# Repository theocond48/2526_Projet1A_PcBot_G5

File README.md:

# 2526_Projet1A_PcBot_G5

**Objectif :** Concevoir un robot communicant (Swarm) pour la cartographie d'environnement.
**Volume horaire :** 40 heures (10 séances x 4h).

- Travail en groupe réalisé par: Youssef Chemrakhi, Théodore Condette, Rayan Taoussi, Samy, Maroua Qidi.

# I - Phase 1 : Conception et Saisie de Schéma
- **Séance 1 : Initialisation & Spécifications**

- **Définition du Besoin**
  - Liste des fonctionnalités
  - Schéma architectural
- **Planification et Matériel**
  - Planning prévisionnel
  - Choix des composants

# 1 - Liste des fonctionnalités
Le robot doit être capable de:
- **Navigation et Évitement d'obstacles :** Détection d'objets en temps réel via les capteurs **VL53L0X (TOF)** pour ajuster la trajectoire.
- **Localisation Relative:** Suivi du déplacement et de l'orientation grâce à la centrale inertielle **LSM6DSOX** (Accéléromètre/Gyroscope).
- **Cartographie Collaborative :** Envoi des points de données de l'environnement vers les autres robots ou une station de base via le module **nRF24**.
- **Gestion de Swarm :** Capacité à recevoir des instructions ou à partager sa position pour éviter que deux robots ne couvrent la même zone.
- **Pilotage de Puissance :** Contrôle précis de la vitesse et de la direction des micro-moteurs **DFR1224** via le driver **DRV8411A**.
- **Autonomie Énergétique :** Recharge sécurisée de la batterie Li-ion et monitoring de la tension via le contrôleur **BQ25896**.

## 1.2 -Détails des composants 

## BMS bq25896

- **C'est quoi ?** Le gestionnaire d'énergie intelligent.
    
- **Sa mission :**
    
    1. Il prend le 5V de l'USB pour charger la batterie LiPo en toute sécurité.
        
    2. Il protège la batterie (surcharge/décharge profonde).
        
    3. Il fournit l'énergie principale (SYS) au reste du robot.
        
- **Pourquoi c'est vital ?** Sans lui, ta batterie LiPo pourrait prendre feu ou mourir prématurément.

### Pin configuration BMS :

**Netlist:**

## Motor's Driver DRV8411A 

- **C'est quoi ?** L'amplificateur de puissance.
    
- **Sa mission :** Le STM32 est trop faible pour faire tourner les moteurs directement. Le DRV8411A prend les petits ordres logiques (3.3V) et ouvre les vannes du "gros courant" venant de la batterie pour faire tourner les roues.
    
- **Pourquoi c'est vital ?** Il protège le STM32 des retours de courant inductif des moteurs.
### Pin configuration Driver

## imu adafruit (centrale inertielle)

 LSM6DSOX (IMU - Accéléromètre/Gyroscope)

- **C'est quoi ?** Le capteur d'équilibre et de mouvement.
    
- **Sa mission :** Il sent si le robot accélère, tourne, ou s'il cogne un mur (choc). Il permet de faire avancer le robot bien droit (en corrigeant la trajectoire si une roue tourne plus vite que l'autre).
    
### Pin configuration imu

## Tof vl53lx
VL53L0X (ToF - Time of Flight)

- **C'est quoi ?** Le télémètre laser.
    
- **Sa mission :** Il envoie un rayon de lumière invisible (infrarouge) et mesure le temps qu'il met à revenir. Cela lui donne la distance précise de l'obstacle devant lui (en millimètres).

### Pin configuration tof

VL53L0X (ToF - Time of Flight)

- **C'est quoi ?** Le télémètre laser.
    
- **Sa mission :** Il envoie un rayon de lumière invisible (infrarouge) et mesure le temps qu'il met à revenir. Cela lui donne la distance précise de l'obstacle devant lui (en millimètres).

## motor DFR1224
(Moteurs N20 3V)

- **C'est quoi ?** Les actionneurs.
    
- **Sa mission :** Convertir l'électricité en mouvement mécanique. Ils ont une boîte de vitesses (engrenages) intégrée pour avoir du couple (force) plutôt que de la vitesse pure.
    
- **Rappel critique :** Ce sont des moteurs **3V**. Ils doivent être alimentés avec précaution via le PWM du driver.

## module de communication nRF24l01

### Pin configuration nrf

**Netlist**

# 2 - Schéma architectural

Le schéma ci-dessous illustre l'organisation du système. Le microcontrôleur (MCU) agit comme le cerveau central, coordonnant les capteurs (entrées), les actionneurs (sorties) et la communication.

```mermaid
graph TD
    %% Alimentation
    subgraph Power_System [Gestion Énergie]
        BAT[Batterie Li-ion] --- BMS[BMS: BQ25896]
        BMS -- I2C --> MCU[STM32L476]
    end

    %% Capteurs
    subgraph Perception [Capteurs / Entrées]
        TOF[Télémètres: VL53L0X] -- I2C --> MCU
        IMU[Centrale Inertielle: LSM6DSOX] -- I2C --> MCU
    end

    %% Communication
    subgraph Comms [Lien Essaim]
        nRF[Radio: nRF24L01] <-->|SPI| MCU
    end

    %% Actionneurs
    subgraph Motion [Actionneurs / Sorties]
        MCU -- PWM --> DRV[Driver: DRV8411]
        DRV --> M1[Moteur Gauche: DFR1224]
        DRV --> M2[Moteur Droit: DFR1224]
    end

    %% Styles
    style MCU fill:#f9f,stroke:#333,stroke-width:2px
    style BMS fill:#dfd
    style nRF fill:#ddf
```

Afin d'assurer les connexions données, on se reposera sur la Datasheet qui nous donne l'ensembles des ports de la STM32L476 qui sont configurés en I2C et SPI:

# 3 - Planning Prévisionnel - Projet PCBot

## Phase 1 : Conception et Saisie de Schéma
- **Séance 1 : Initialisation & Spécifications**
  - Formation du groupe.
  - Création du dépôt Git et ajout du professeur (laurent.fiack@ensea.fr).
  - Étude des composants : Capteurs TOF, Accéléromètre, nRF24, Batterie/Chargeur.
- **Séance 2 : Saisie de schéma**
  - Début de la saisie sur KiCad des blocs d'alimentation et du microcontrôleur.
- **Séance 3 : Revue de schéma & Finalisation**
  - Revue critique des connexions.
  - Finalisation du schéma complet avant les vacances de février.

## Phase 2 : Routage et Fabrication
- **Séance 4 : Placement et Routage**
  - Placement des composants sur le PCB.
  - Routage des pistes.
- **Séance 5 : Revue de routage & Commande**
  - **Critique :** Validation finale du routage.
  - Génération et envoi des fichiers de fabrication (Gerber).

## Phase 3 : Firmware et Intégration
- **Séance 6 : Tests préliminaires & Firmware**
  - Tests sur cartes de développement.
  - Développement des drivers pour les capteurs TOF et le module nRF24.
- **Séance 7 : Développement Firmware**
  - Implémentation des algorithmes de cartographie et de communication Swarm.
- **Séance 8 : Firmware & Soudure**
  - Réception possible des PCB.
  - Assemblage (soudure) et tests de continuité.
- **Séance 9 : Intégration Finale & Débogage**
  - Tests en conditions réelles du robot.
  - Correction des derniers bugs du firmware.

## Phase 4 : Clôture
- **Séance 10 : Finitions & Démo**
  - 2h : Préparation finale et finitions.
  - 2h : Présentation et démonstration du projet.

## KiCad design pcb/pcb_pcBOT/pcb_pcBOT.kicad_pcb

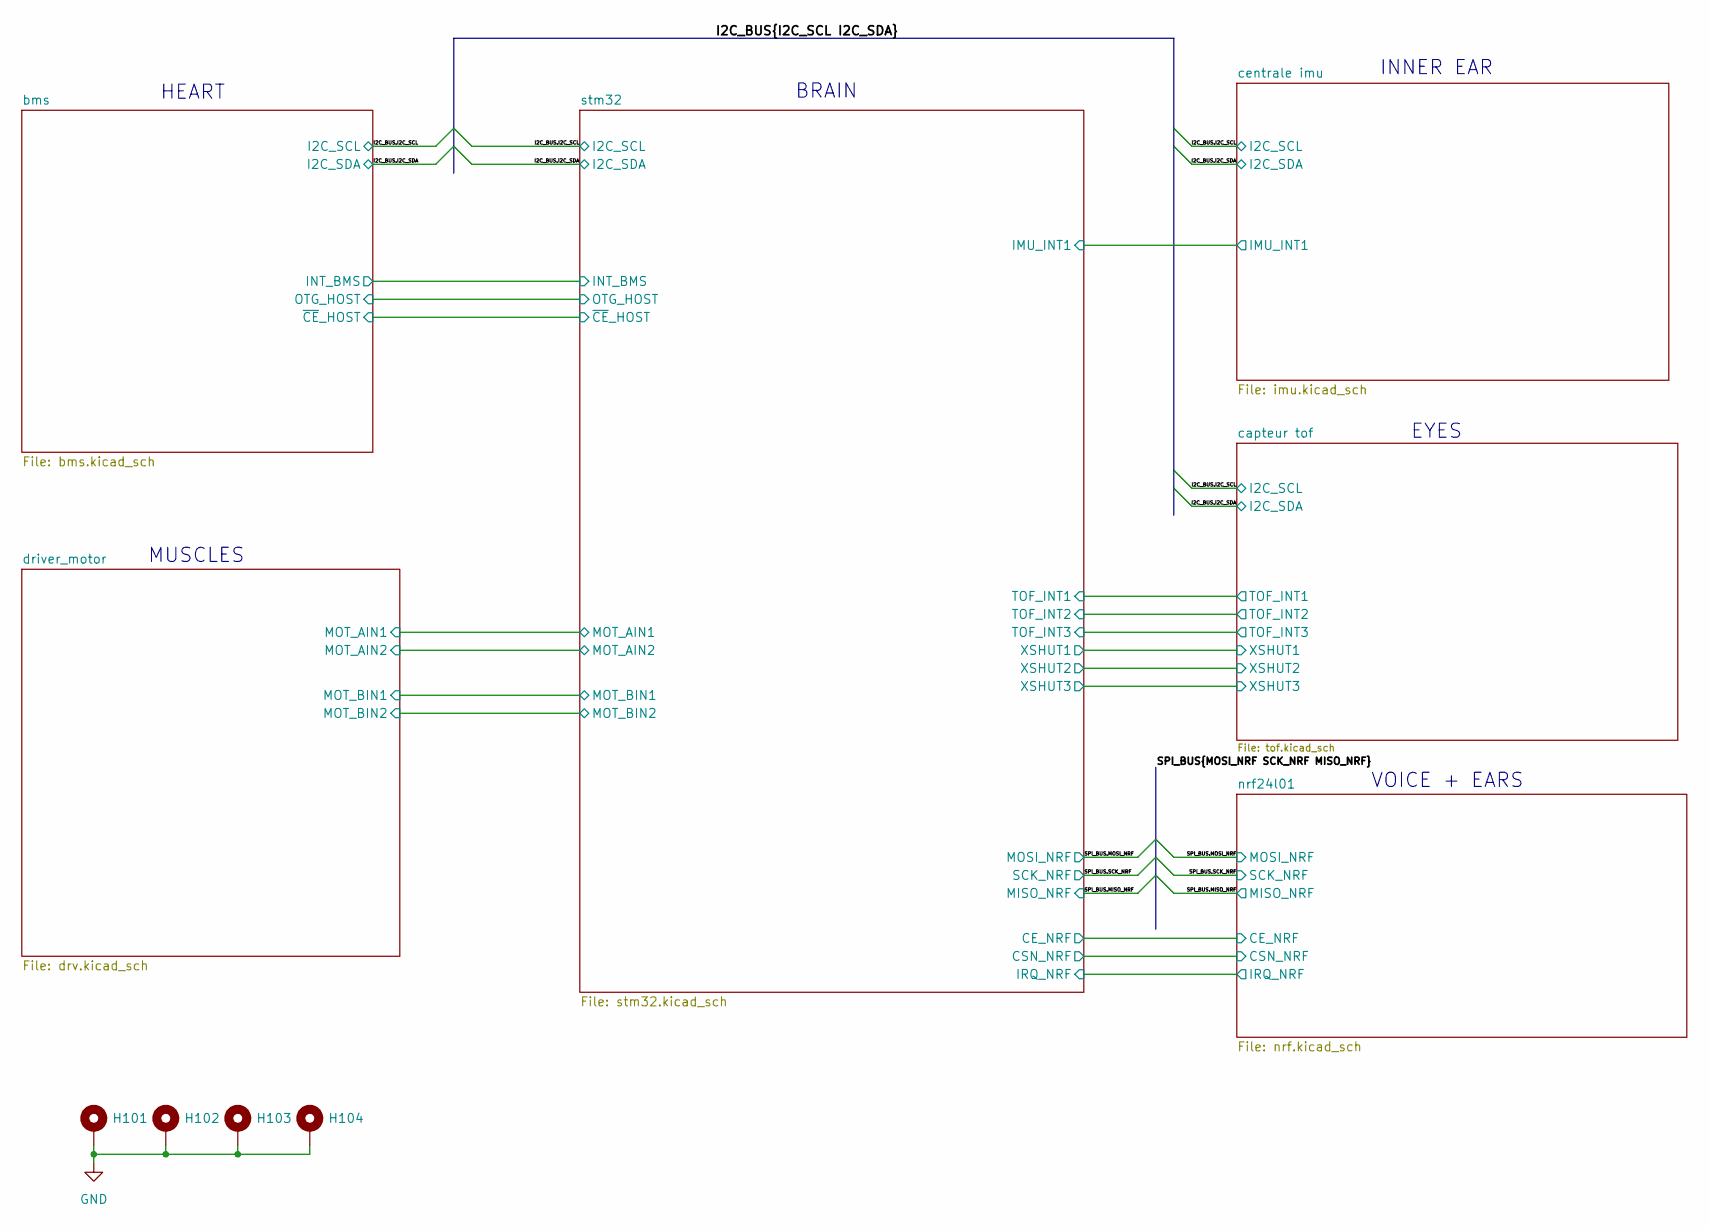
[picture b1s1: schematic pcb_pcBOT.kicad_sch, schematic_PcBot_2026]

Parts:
H101, H102, H103, H104: MountingHole_Pad; MountingHole_3.2mm_M3_Pad_Via

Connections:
GND: H101.1, H102.1, H103.1, H104.1; also elsewhere on the board

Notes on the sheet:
BRAIN
EYES
HEART
VOICE + EARS
INNER EAR
MUSCLES

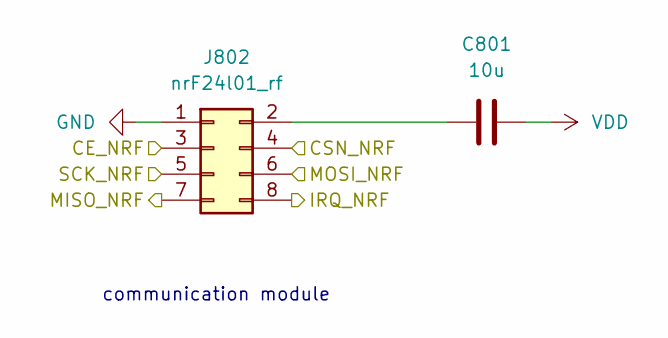
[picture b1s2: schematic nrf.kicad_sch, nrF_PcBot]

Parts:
C801: 10u; C_0603_1608Metric
J802: nrF24l01_rf; PinHeader_2x04_P2.54mm_Vertical

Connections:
/SPI_BUS.MISO_NRF: J802.7; also elsewhere on the board
/SPI_BUS.MOSI_NRF: J802.6; also elsewhere on the board
/SPI_BUS.SCK_NRF: J802.5; also elsewhere on the board
/nrf24l01/CE_NRF: J802.3; also elsewhere on the board
/nrf24l01/CSN_NRF: J802.4; also elsewhere on the board
/nrf24l01/IRQ_NRF: J802.8; also elsewhere on the board
GND: J802.1; also elsewhere on the board
unnamed: C801.1, J802.2
VDD: C801.2; also elsewhere on the board

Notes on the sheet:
communication module

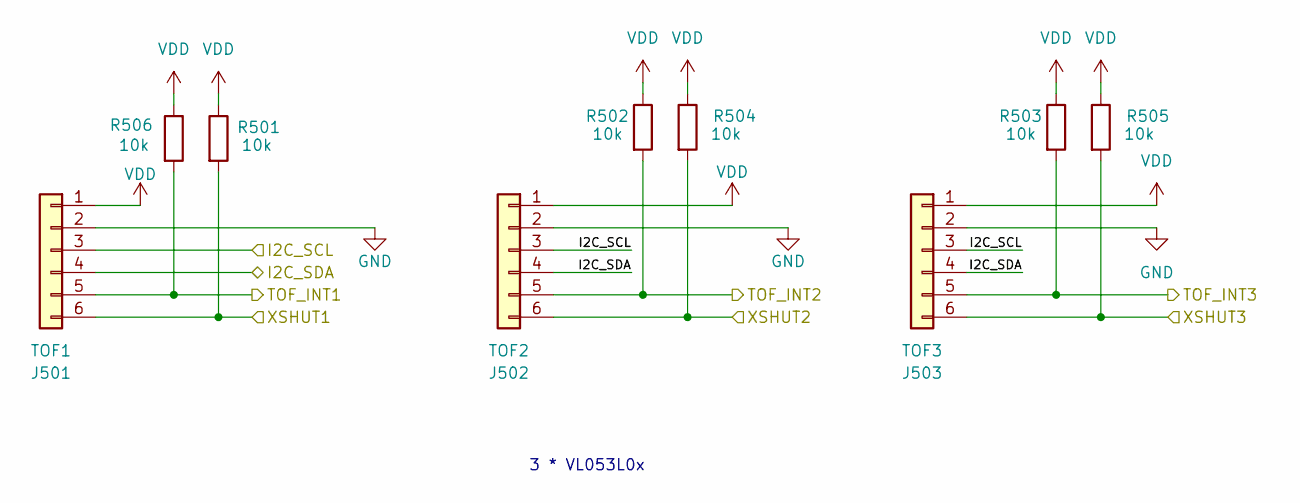
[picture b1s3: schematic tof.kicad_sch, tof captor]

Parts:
J501: TOF1; PinSocket_1x06_P2.54mm_Vertical
J502: TOF2; PinSocket_1x06_P2.54mm_Vertical
J503: TOF3; PinSocket_1x06_P2.54mm_Vertical
R501, R502, R503, R504, R505, R506: 10k; R_0402_1005Metric

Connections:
/I2C_BUS.I2C_SCL: J501.3, J502.3, J503.3; also elsewhere on the board
/I2C_BUS.I2C_SDA: J501.4, J502.4, J503.4; also elsewhere on the board
/capteur tof/TOF_INT1: J501.5, R506.2; also elsewhere on the board
/capteur tof/TOF_INT2: J502.5, R502.2; also elsewhere on the board
/capteur tof/TOF_INT3: J503.5, R503.2; also elsewhere on the board
/capteur tof/XSHUT1: J501.6, R501.2; also elsewhere on the board
/capteur tof/XSHUT2: J502.6, R504.2; also elsewhere on the board
/capteur tof/XSHUT3: J503.6, R505.2; also elsewhere on the board
GND: J501.2, J502.2, J503.2; also elsewhere on the board
VDD: J501.1, J502.1, J503.1, R501.1, R502.1, R503.1, R504.1, R505.1, R506.1; also elsewhere on the board

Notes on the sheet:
3 * VL053L0x

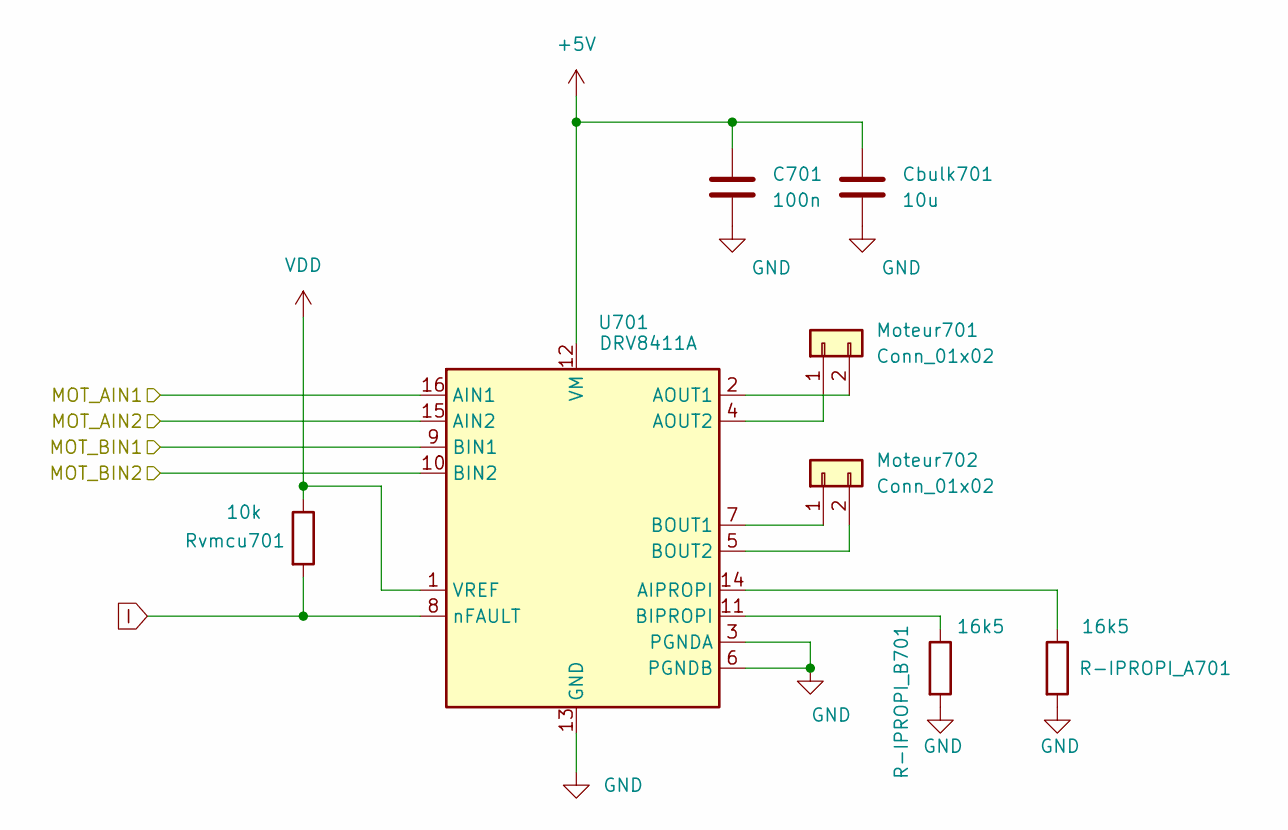
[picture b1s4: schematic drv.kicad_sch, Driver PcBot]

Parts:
C701: 100n; C_0402_1005Metric
Cbulk701: 10u; C_0603_1608Metric
Moteur701, Moteur702: Conn_01x02; JST_PH_B2B-PH-K_1x02_P2.00mm_Vertical
R-IPROPI_A701: 16k5; R_0402_1005Metric
R-IPROPI_B701: 16k5; R_0402_1005Metric
Rvmcu701: 10k; R_0402_1005Metric
U701: DRV8411A; HTSSOP-16-1EP_4.4x5mm_P0.65mm_EP3.4x5mm_Mask2.46x2.31mm_The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

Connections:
+5V: C701.2, Cbulk701.1, U701.12 (VM); also elsewhere on the board
/driver_motor/MOT_AIN1: U701.16 (AIN1); also elsewhere on the board
/driver_motor/MOT_AIN2: U701.15 (AIN2); also elsewhere on the board
/driver_motor/MOT_BIN1: U701.9 (BIN1); also elsewhere on the board
/driver_motor/MOT_BIN2: U701.10 (BIN2); also elsewhere on the board
GND: C701.1, Cbulk701.2, R-IPROPI_A701.2, R-IPROPI_B701.2, U701.3 (PGNDA), U701.6 (PGNDB), U701.13 (GND), U701.17 (PPAD); also elsewhere on the board
I: Rvmcu701.2, U701.8 (nFAULT)
unnamed: Moteur701.1, U701.4 (AOUT2)
unnamed: Moteur701.2, U701.2 (AOUT1)
unnamed: Moteur702.1, U701.7 (BOUT1)
unnamed: Moteur702.2, U701.5 (BOUT2)
unnamed: R-IPROPI_A701.1, U701.14 (AIPROPI)
unnamed 52: R-IPROPI_B701.1, U701.11 (BIPROPI); also elsewhere on the board
VDD: Rvmcu701.1, U701.1 (VREF); also elsewhere on the board

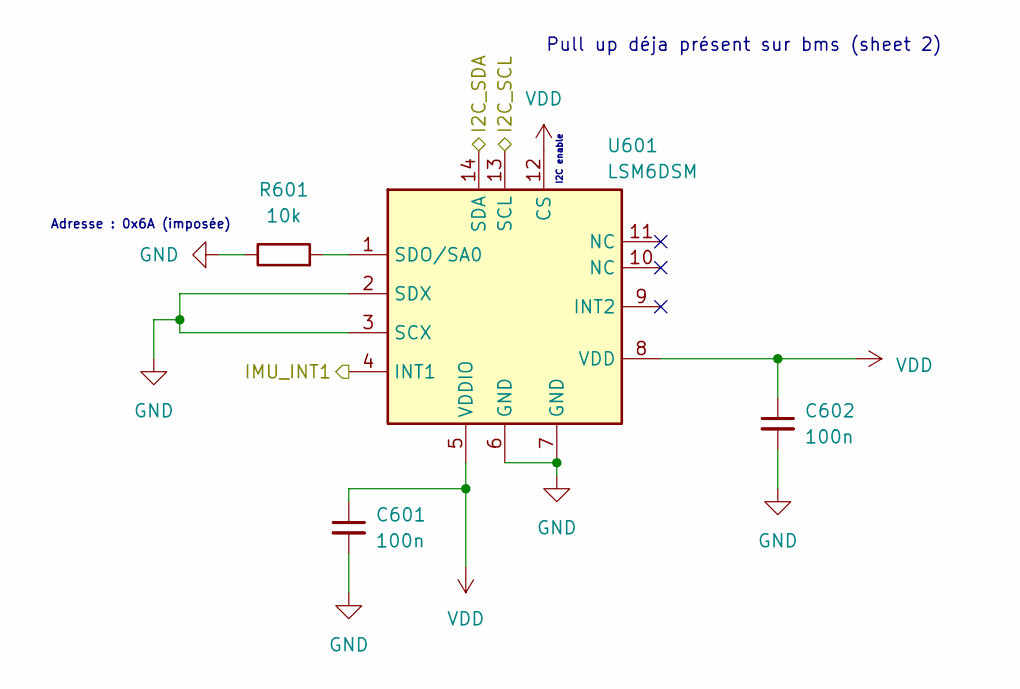
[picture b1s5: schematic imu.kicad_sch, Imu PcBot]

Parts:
C601, C602: 100n; C_0402_1005Metric
R601: 10k; R_0402_1005Metric
U601: LSM6DSM; LGA-14_3x2.5mm_P0.5mm_LayoutBorder3x4y

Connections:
/I2C_BUS.I2C_SCL: U601.13 (SCL); also elsewhere on the board
/I2C_BUS.I2C_SDA: U601.14 (SDA); also elsewhere on the board
/centrale imu/IMU_INT1: U601.4 (INT1); also elsewhere on the board
GND: C601.2, C602.2, R601.1, U601.2 (SDX), U601.3 (SCX), U601.6 (GND), U601.7 (GND); also elsewhere on the board
unnamed: R601.2, U601.1 (SDO/SA0)
VDD: C601.1, C602.1, U601.5 (VDDIO), U601.8 (VDD), U601.12 (CS); also elsewhere on the board

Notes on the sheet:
I2C enable
Pull up déja présent sur bms (sheet 2)
Adresse : 0x6A (imposée)

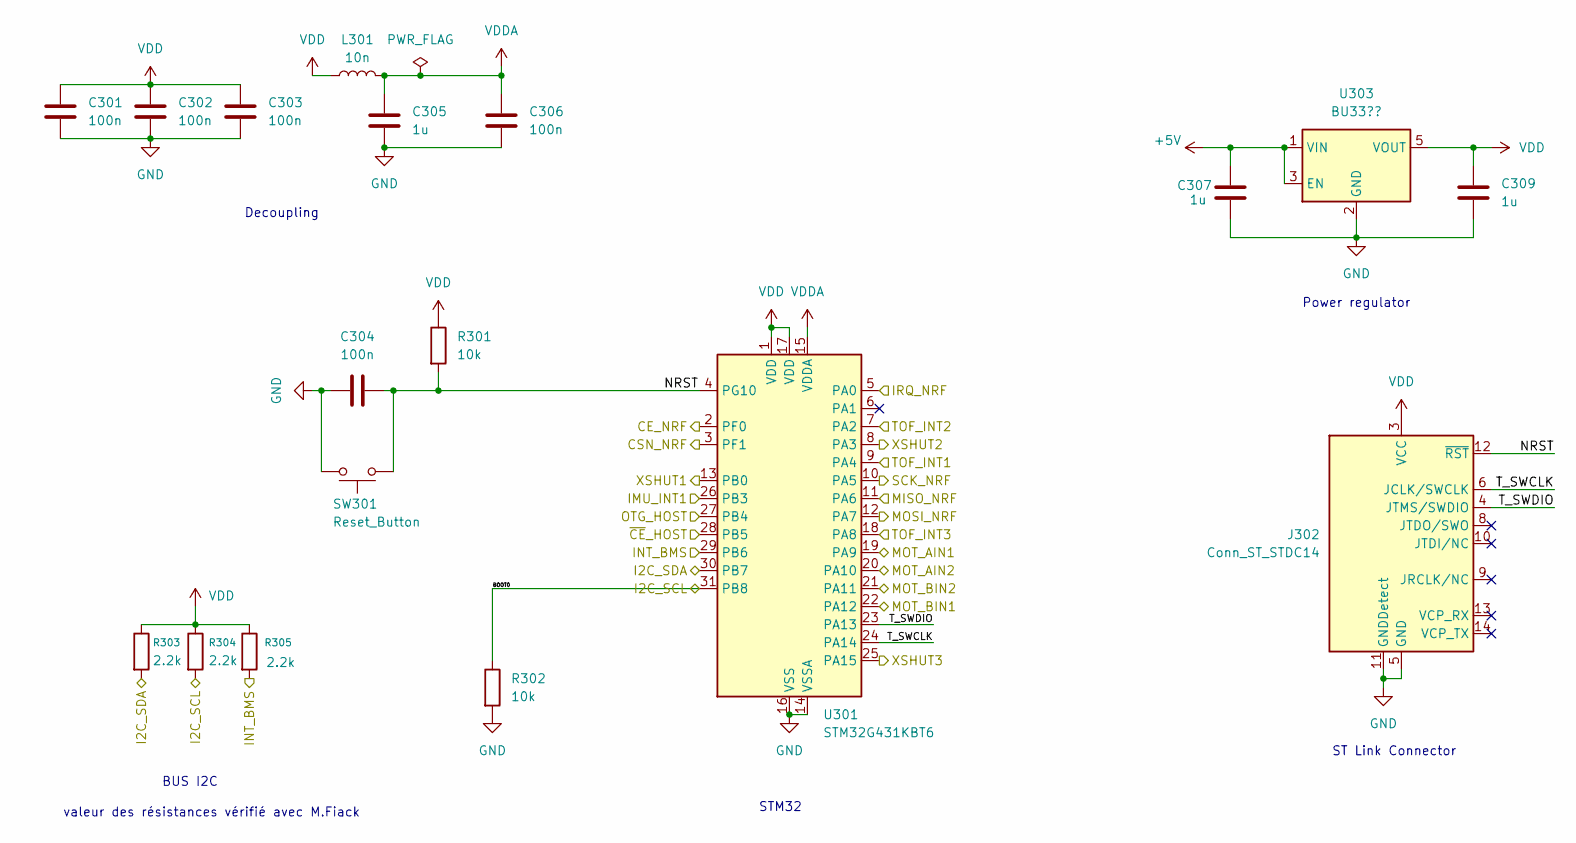
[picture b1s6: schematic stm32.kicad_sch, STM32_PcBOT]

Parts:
C301, C302, C303, C304, C306: 100n; C_0402_1005Metric
C305, C307, C309: 1u; C_0402_1005Metric
J302: Conn_ST_STDC14; PinHeader_2x07_P1.27mm_Vertical_SMD
L301: 10n; C_0603_1608Metric
R301, R302: 10k; R_0402_1005Metric
R303, R304, R305: 2.2k; R_0402_1005Metric
SW301: Reset_Button; SW_PUSH_6mm
U301: STM32G431KBT6; LQFP-32_7x7mm_P0.8mm
U303: BU33??; TSOT-23-5

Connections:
+5V: C307.1, U303.1 (VIN), U303.3 (EN); also elsewhere on the board
/I2C_BUS.I2C_SCL: R302.1, R304.2, U301.31 (PB8); also elsewhere on the board
/I2C_BUS.I2C_SDA: R303.2, U301.30 (PB7); also elsewhere on the board
/SPI_BUS.MISO_NRF: U301.11 (PA6); also elsewhere on the board
/SPI_BUS.MOSI_NRF: U301.12 (PA7); also elsewhere on the board
/SPI_BUS.SCK_NRF: U301.10 (PA5); also elsewhere on the board
/bms/INT_BMS: R305.2, U301.29 (PB6); also elsewhere on the board
/bms/OTG_HOST: U301.27 (PB4); also elsewhere on the board
/bms/~CE_HOST: U301.28 (PB5); also elsewhere on the board
/capteur tof/TOF_INT1: U301.9 (PA4); also elsewhere on the board
/capteur tof/TOF_INT2: U301.7 (PA2); also elsewhere on the board
/capteur tof/TOF_INT3: U301.18 (PA8); also elsewhere on the board
/capteur tof/XSHUT1: U301.13 (PB0); also elsewhere on the board
/capteur tof/XSHUT2: U301.8 (PA3); also elsewhere on the board
/capteur tof/XSHUT3: U301.25 (PA15); also elsewhere on the board
/centrale imu/IMU_INT1: U301.26 (PB3); also elsewhere on the board
/driver_motor/MOT_AIN1: U301.19 (PA9); also elsewhere on the board
/driver_motor/MOT_AIN2: U301.20 (PA10); also elsewhere on the board
/driver_motor/MOT_BIN1: U301.22 (PA12); also elsewhere on the board
/driver_motor/MOT_BIN2: U301.21 (PA11); also elsewhere on the board
/nrf24l01/CE_NRF: U301.2 (PF0); also elsewhere on the board
/nrf24l01/CSN_NRF: U301.3 (PF1); also elsewhere on the board
/nrf24l01/IRQ_NRF: U301.5 (PA0); also elsewhere on the board
/stm32/NRST: C304.1, J302.12 (~RST), R301.2, SW301.1, U301.4 (PG10)
/stm32/T_SWCLK: J302.6 (JCLK/SWCLK), U301.24 (PA14)
/stm32/T_SWDIO: J302.4 (JTMS/SWDIO), U301.23 (PA13)
GND: C301.2, C302.2, C303.2, C304.2, C305.2, C306.2, C307.2, C309.2, J302.5 (GND), J302.7 (GND), J302.11 (GNDDetect), R302.2, SW301.2, U301.14 (VSSA), U301.16 (VSS), U301.32 (VSS), U303.2 (GND); also elsewhere on the board
VDD: C301.1, C302.1, C303.1, C309.1, J302.3 (VCC), L301.1, R301.1, R303.1, R304.1, R305.1, U301.1 (VDD), U301.17 (VDD), U303.5 (VOUT); also elsewhere on the board
VDDA: C305.1, C306.1, L301.2, U301.15 (VDDA)

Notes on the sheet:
ST Link Connector
BUS I2C
Decoupling
valeur des résistances vérifié avec M.Fiack
Power regulator
STM32

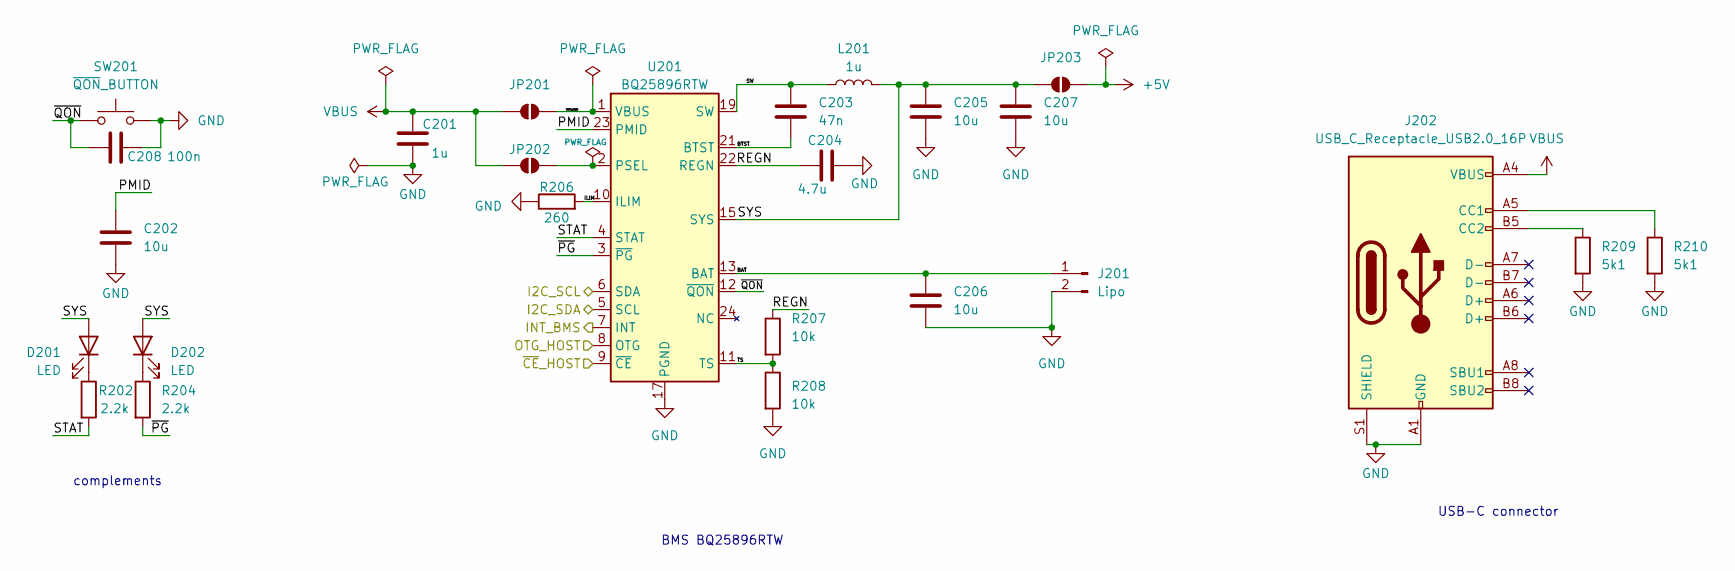
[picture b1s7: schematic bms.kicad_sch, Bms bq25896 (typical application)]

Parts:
C201: 1u; C_0402_1005Metric
C202, C205, C206, C207: 10u; C_0603_1608Metric
C203: 47n; C_0402_1005Metric
C204: 4.7u; C_0603_1608Metric
C208: 100n; C_0402_1005Metric
D201, D202: LED; C_0402_1005Metric
J201: Lipo; JST_PH_B2B-PH-K_1x02_P2.00mm_Vertical
J202: USB_C_Receptacle_USB2.0_16P; USB_C_Receptacle_GCT_USB4105-xx-A_16P_TopMnt_Horizontal
JP201, JP202, JP203: SolderJumper_2_Open; SolderJumper-2_P1.3mm_Open_TrianglePad1.0x1.5mm
L201: 1u; L_1008_2520Metric
R202, R204: 2.2k; R_0402_1005Metric
R206: 260; R_0402_1005Metric
R207, R208: 10k; R_0402_1005Metric
R209, R210: 5k1; R_0402_1005Metric
SW201: ~{QON}_BUTTON; SW_PUSH_6mm
U201: BQ25896RTW; Texas_RTW_WQFN-24-1EP_4x4mm_P0.5mm_EP2.7x2.7mm_ThermalVias

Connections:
+5V: JP203.2 (B); also elsewhere on the board
/I2C_BUS.I2C_SCL: U201.6 (SDA); also elsewhere on the board
/I2C_BUS.I2C_SDA: U201.5 (SCL); also elsewhere on the board
/bms/BAT: C206.1, J201.1, U201.13 (BAT), U201.14 (BAT)
/bms/BTST: C203.2, U201.21 (BTST)
/bms/ILIM: R206.2, U201.10 (ILIM)
/bms/INT_BMS: U201.7 (INT); also elsewhere on the board
/bms/OTG_HOST: U201.8 (OTG); also elsewhere on the board
/bms/PMID: C202.1, U201.23 (PMID)
/bms/REGN: C204.2, R207.1, U201.22 (REGN)
/bms/STAT: R202.2, U201.4 (STAT)
/bms/SW: C203.1, L201.1, U201.19 (SW), U201.20 (SW)
/bms/SYS: C205.1, C207.1, D201.2 (A), D202.2 (A), JP203.1 (A), L201.2, U201.15 (SYS), U201.16 (SYS)
/bms/TS: R207.2, R208.1, U201.11 (TS)
/bms/VBUS_BQ25: JP201.2 (B), U201.1 (VBUS)
/bms/~CE_HOST: U201.9 (~CE); also elsewhere on the board
/bms/~PG: R204.2, U201.3 (~PG)
/bms/~QON: C208.1, SW201.1, U201.12 (~QON)
GND: C201.2, C202.2, C204.1, C205.2, C206.2, C207.2, C208.2, J201.2, J202.A1 (GND), J202.A12 (GND), J202.B1 (GND), J202.B12 (GND), J202.S1 (SHIELD), R206.1, R208.2, R209.2, R210.2, SW201.2, U201.17 (PGND), U201.18 (PGND), U201.25 (PGND); also elsewhere on the board
unnamed: D201.1 (K), R202.1
unnamed: D202.1 (K), R204.1
unnamed: J202.A5 (CC1), R210.1
unnamed: J202.B5 (CC2), R209.1
unnamed: JP202.2 (B), U201.2 (PSEL)
VBUS: C201.1, J202.A4 (VBUS), J202.A9 (VBUS), J202.B4 (VBUS), J202.B9 (VBUS), JP201.1 (A), JP202.1 (A)

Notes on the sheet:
USB-C connector
BMS BQ25896RTW
complements

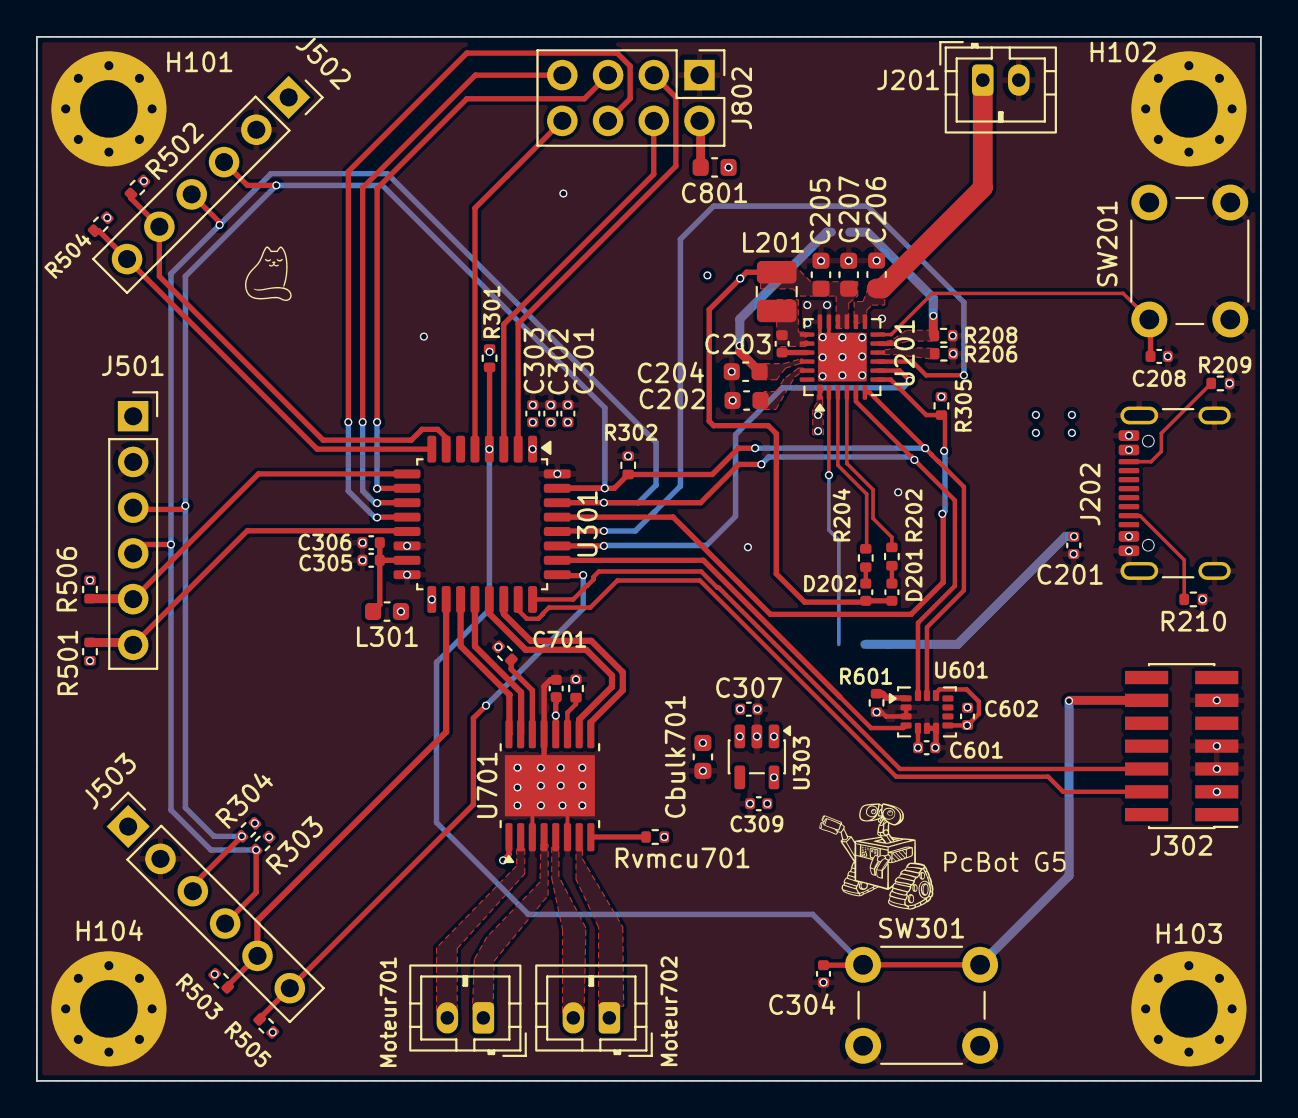
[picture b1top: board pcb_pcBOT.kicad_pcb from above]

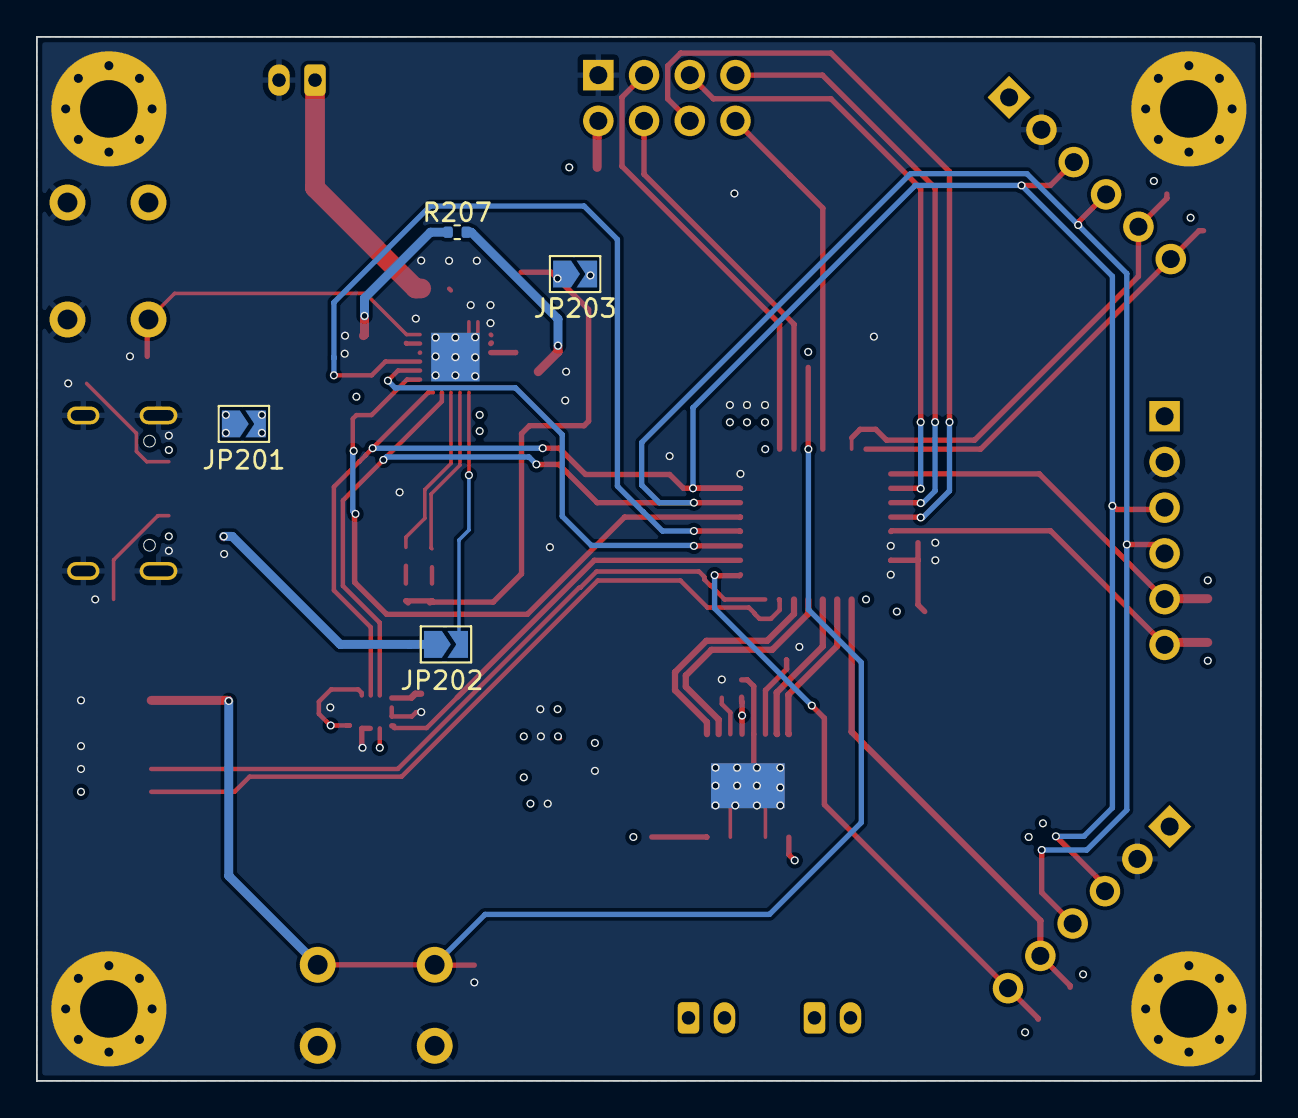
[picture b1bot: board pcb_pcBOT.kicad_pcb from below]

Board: 4 copper layers, 68.0 x 58.0 mm, 70 parts (4 on the bottom side), 56 nets.

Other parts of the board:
R-B701: 16k5; R_0402_1005Metric

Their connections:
GND: R-B701.2; also elsewhere on the board
unnamed 52: R-B701.1; also elsewhere on the board

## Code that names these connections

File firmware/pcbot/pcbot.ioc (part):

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Mcu.Name=STM32G431K(6-8-B)Tx
Mcu.Package=LQFP32
Mcu.UserName=STM32G431KBTx
PA0.GPIOParameters=GPIO_Label
PA0.GPIO_Label=IRQ_NRF
PA0.Signal=GPXTI0
PA10.GPIOParameters=GPIO_Label
PA10.GPIO_Label=MOT_AIN2
PA10.Signal=S_TIM1_CH3
PA11.GPIOParameters=GPIO_Label
PA11.GPIO_Label=MOT_BIN2
PA11.Mode=PWM Generation1 CH1N
PA11.Signal=TIM1_CH1N
PA12.GPIOParameters=GPIO_Label
PA12.GPIO_Label=MOT_BIN1
PA12.Mode=PWM Generation2 CH2N
PA12.Signal=TIM1_CH2N
PA13.Mode=Serial_Wire
PA13.Signal=SYS_JTMS-SWDIO
PA14.Mode=Serial_Wire
PA14.Signal=SYS_JTCK-SWCLK
PA15.GPIOParameters=GPIO_Label
PA15.GPIO_Label=XSHUT3
PA15.Signal=GPIO_Output
PA2.GPIOParameters=GPIO_Label
PA2.GPIO_Label=TOF_INT2
PA2.Signal=GPIO_Input
PA3.GPIOParameters=GPIO_Label
PA3.GPIO_Label=XSHUT2
PA3.Signal=GPIO_Output
PA4.GPIOParameters=GPIO_Label
PA4.GPIO_Label=TOF_INT1
PA4.Signal=GPIO_Input
PA5.Signal=SPI1_SCK
PA6.Signal=SPI1_MISO
PA7.Signal=SPI1_MOSI
PA8.GPIOParameters=GPIO_Label
PA8.GPIO_Label=TOF_INT3
PA8.Signal=GPIO_Input
PA9.GPIOParameters=GPIO_Label
PA9.GPIO_Label=MOT_AIN1
PA9.Signal=S_TIM2_CH3
PB0.GPIOParameters=GPIO_Label
PB0.GPIO_Label=XSHUT1
PB0.Signal=GPIO_Output
PB3.GPIOParameters=GPIO_Label
PB3.GPIO_Label=IMU_INT1
PB3.Signal=GPIO_Input
PB4.GPIOParameters=GPIO_Label
PB4.GPIO_Label=OTG_BMS
PB4.Signal=GPIO_Output
PB5.GPIOParameters=GPIO_Label
PB5.GPIO_Label=CE_BMS
PB5.Signal=GPIO_Output
PB6.GPIOParameters=GPIO_Label
PB6.GPIO_Label=INT_BMS
PB6.Signal=GPIO_Input
PB7.Mode=I2C
PB7.Signal=I2C1_SDA
PB8-BOOT0.Mode=I2C
PB8-BOOT0.Signal=I2C1_SCL
PF0-OSC_IN.GPIOParameters=GPIO_Label
PF0-OSC_IN.GPIO_Label=CE_NRF
PF0-OSC_IN.Signal=GPIO_Output
PF1-OSC_OUT.GPIOParameters=GPIO_Label
PF1-OSC_OUT.GPIO_Label=CSN_NRF
PF1-OSC_OUT.Signal=GPIO_Output
RCC.HSE_VALUE=8000000
RCC.SYSCLKFreq_VALUE=16000000
board=custom

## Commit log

2026-02-05 modifications test
2026-02-05 j'ai enlevé les modifications
2026-02-05 j'ai ajouté un fichier test md
2026-02-05 Create tests
2026-02-05 j'ai modifie mon fichier tests
2026-02-05 fiche technique du BMS
2026-02-05 j'ai clean le ficher
2026-02-05 J'ai modifié le fichier Readme
2026-02-05 j'ai modifié tout
2026-02-05 plus de doc
2026-02-05 j'ai ajoute les datasheets
2026-02-08 J'ai modifié le fichier READme et j'ai ajouté l'ensemble des documentations sur le fichier Documentation
2026-02-08 Modifs
2026-02-08 Modifs de READme
2026-02-09 J'ai ajouté la Datasheet I2C,SPI
2026-02-09 Modifs de nouveau
2026-02-09 J'ai enlevé les rappels git
2026-02-09 J'ai ajt une branche
2026-02-09 correction probleme read.me
2026-02-09 J'ai ajouté des commandes utiles de git
2026-02-09 je fix les problèmes d'images
2026-02-11 rien
2026-02-11 last fix pls
2026-02-12 j'ai juste modifie mon prenom
2026-02-12 j'ai ajoute comment on fait un merge sur Github
2026-02-12 j'ai ajoute la commande pour creer une branche
2026-02-12 creation du fichier pcb et des feuilles kicad
2026-02-12 ajout de la librairie composant
2026-02-12 avancement sur le schematic bms
2026-02-13 schematic bms( in progress)
2026-02-19 tente un push
2026-02-19 Description de mes changements
2026-02-19 update bms
2026-02-19 DRV fini
2026-02-19 fin bms schematic bms
2026-02-19 manual merge
2026-02-19 Schema du stm32
2026-02-19 stm32 (in progress)
2026-02-19 small adjustments
2026-02-22 avancement des schematics
2026-02-22 ajout du module nrf + petites corrections
2026-03-04 Mise à jour du schéma TOF
2026-03-06 complement tof et connections, mise a jour du firmware
2026-03-09 corrections d'erreurs et liasons bus i2c et spi
2026-03-10 Ajout empreintes (incomplet) + test erc correct
2026-03-12 Revert "Ajout empreintes (incomplet) + test erc correct"
    This reverts commit 267ed5519d67c336b99c9c80b0ac2067182b82a3.
2026-03-12 fix pitié
2026-03-12 fix final
2026-03-12 fin de schematique
2026-03-12 schematique terminé + probleme empreinte réglé + début routage
2026-03-16 début routage premier jet
2026-03-19 routage wip
2026-03-19 rouatage + firmware wip
2026-03-24 routage wip encore
2026-03-26 fin du routage
2026-03-26 pcb v1 fini fichier envoyé à jlc
2026-04-01 code genérer du ioc du stm du pcb
2026-04-01 Robot codes
2026-04-01 ajout lib
2026-04-01 tof codes
2026-04-01 COMMANDS TOF
2026-04-01 Codes IMU
2026-04-01 fix errur pin imu_int
2026-04-09 Codes
2026-04-09 code driver
2026-04-09 ajout du code de Tof_Read
